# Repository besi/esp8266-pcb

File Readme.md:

ESP8266 PCB
===========

Flashing
--------

The 16MB flash chip need some special settings when flashing:

	esptool.py -p /dev/cu.usbserial-1412440 \
    -c esp8266 -b 460800 write_flash -fm dio \
    --flash_size=16MB \
    0x0000 ~/Downloads/ESP8266_GENERIC-20240222-v1.22.2.bin \
    0xffc000 ~/esp/esp-idf/components/esptool_py/esptool/test/images/esp8266_sdk/esp_init_data_default.bin

JLCPCB Footprints
-----------------

I created the following alias to download the footprints:

    # ~/.zshrc
    alias jlc='JLC2KiCadLib -dir lib -symbol_lib jlc_symbols -symbol_lib_dir "." -footprint_lib jlc_footprints.pretty'

So I can for example run `jlc C123455` to download both the symbol and the footprint for a given component.

    jlc C77967 --no_symbol # ESP8266EX chip
    jlc C505111 --no_symbol # Micro USB adapter
    jlc C7464026 --no_symbol # USB2UART chip
    jlc C160390 # I2C connector
    jlc C82227 # Temperature and humidity sensor
    jlc C2922787 # SK6812 Neopixel
    jlc C51118 # 3V3 AP2112K voltage regulator
    jlc C62892 # NPN transistor array
    jlc C318884 # Tactile switches
    jlc C424093 # Battery management IC
    jlc C97521 # flash chip (alternative: C5127618)
    jlc C295747 # JST battery connector
    jlc C963206 # slide switch
    jlc C15127 # FET for switching between VUSB and VBAT
    jlc C155590 # Zener Diode D3
    
    jlc C22975 # 2k R4
    jlc C19666 # 4.7uF
    jlc C25804 # 10k
    jlc C155590 # Shottkydiode D3
    jlc C15127 # p channel mosfet
    jlc C15849 # 1uF
    jlc C23630 # 2.2uF
    jlc C19702 # 10uF
    jlc C14663 # 100nF
    jlc C255886 # 26Mhz oscilator
    jlc C1634 # 10pF
    jlc C22790 # 12k
    jlc C8218 # 200 Ohm
    jlc C519111 # 5.6pF
        
Credits
-------

- I used the wonderful [JLC2KiCadLib](https://pypi.org/project/JLC2KiCadLib/) to get the footprints from the JLC components.
- This design was inspired by the [Sparkfun ESP8266 Thing](https://www.sparkfun.com/sparkfun-esp8266-thing.html)

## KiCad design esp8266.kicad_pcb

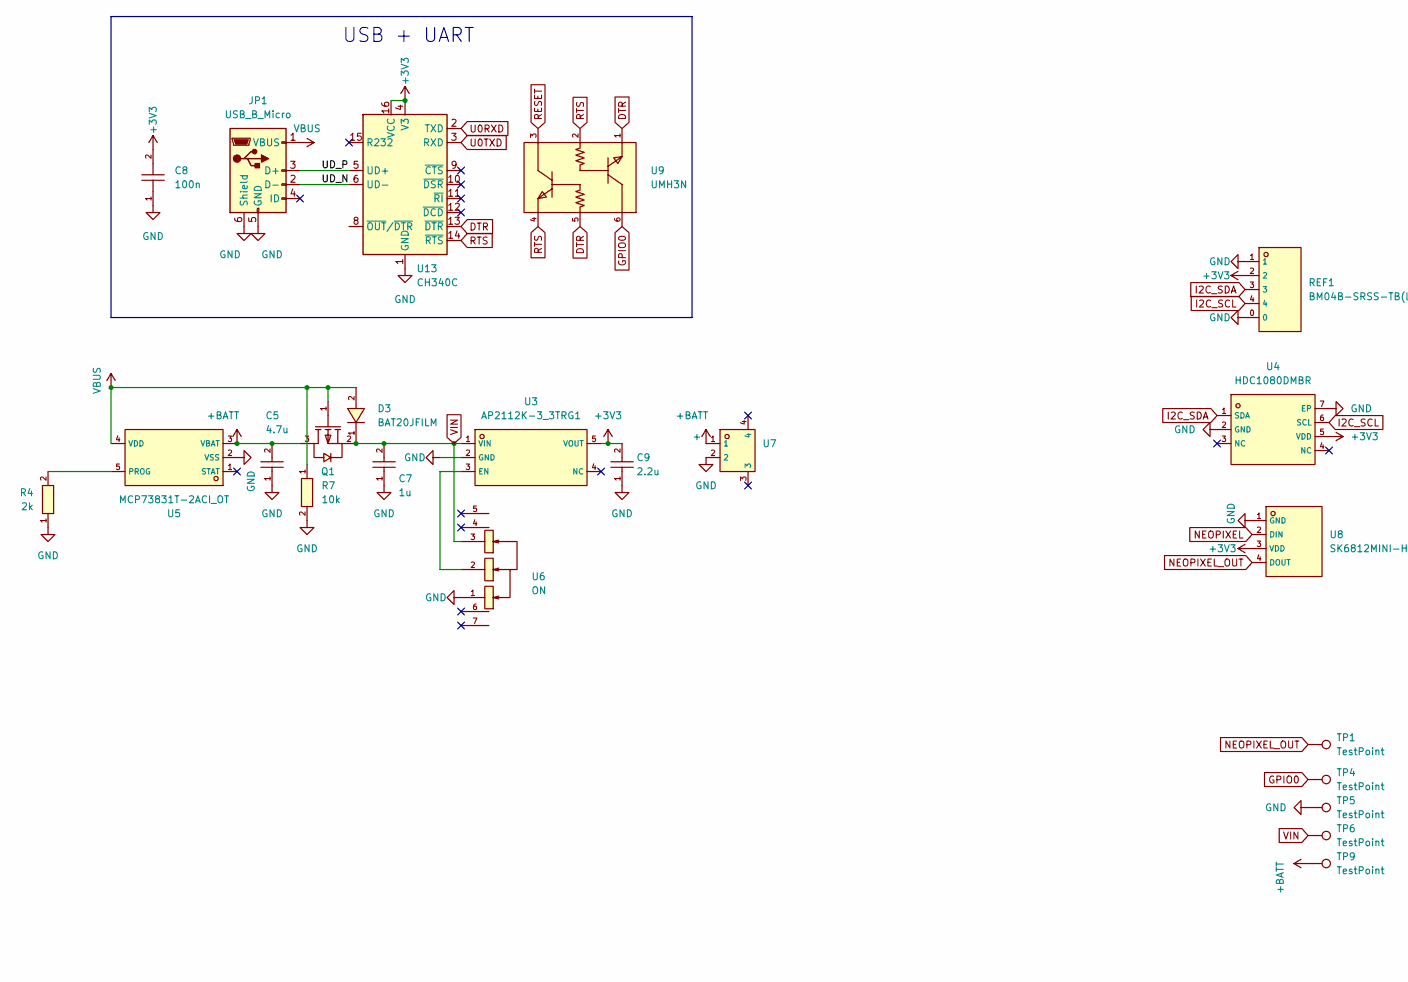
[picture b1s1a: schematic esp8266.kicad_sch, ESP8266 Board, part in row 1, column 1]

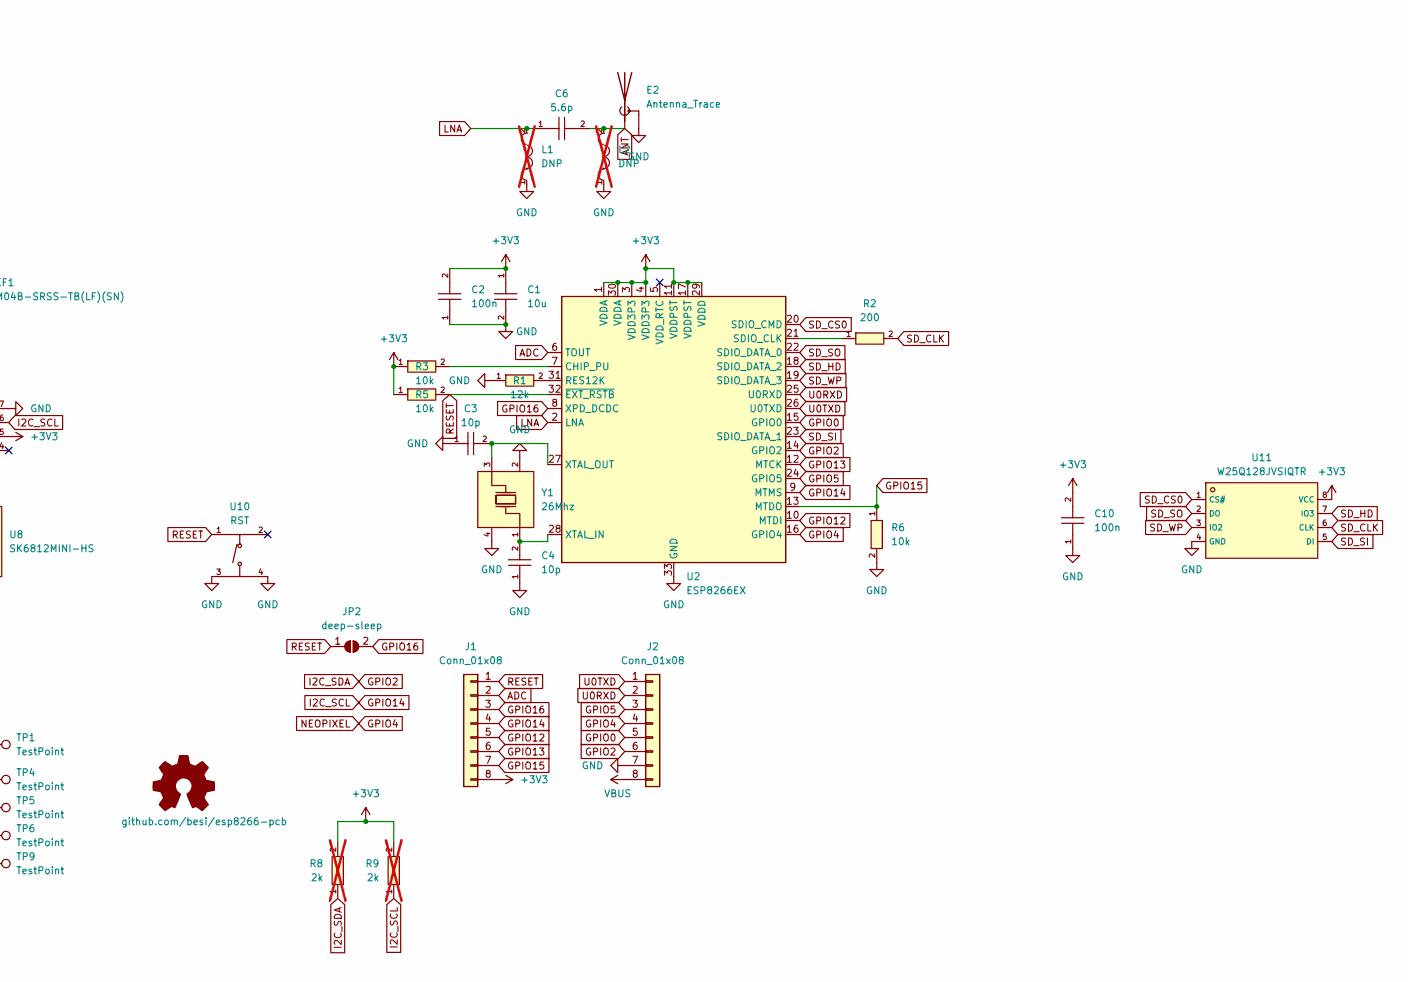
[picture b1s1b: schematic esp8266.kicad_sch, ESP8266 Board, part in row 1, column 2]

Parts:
C1: 10u; C0603; LCSC C19702
C2, C8, C10: 100n; C0603; LCSC C14663
C3, C4: 10p; C0603; LCSC C1634
C5: 4.7u; C0603; LCSC C19666
C6: 5.6p; C0603; LCSC C519111
C7: 1u; C0603; LCSC C15849
C9: 2.2u; C0603; LCSC C23630
D3: BAT20JFILM; SOD-323_L1.8-W1.3-LS2.5-RD; LCSC C155590
E2: Antenna_Trace; Texas_SWRA117D_2.4GHz_Right
J1, J2: Conn_01x08; PinHeader_1x08_P2.54mm_Vertical
JP1: USB_B_Micro; MICRO-USB-SMD_1050171001; LCSC C505111
JP2: deep-sleep; SolderJumper-2_P1.3mm_Open_TrianglePad1.0x1.5mm
L1, L2: DNP; L0603; LCSC C1035; not fitted
OSHW1: github.com/besi/esp8266-pcb; OSHW-Symbol_6.7x6mm_SilkScreen
Q1: AO3401A; SOT-23_L2.9-W1.3-P1.90-LS2.4-BR; LCSC C15127
R1: 12k; R0603; LCSC C22790
R2: 200; R0603; LCSC C8218
R3, R5, R6, R7: 10k; R0603; LCSC C25804
R4: 2k; R0603; LCSC C22975
R8, R9: 2k; R_0603_1608Metric_Pad0.98x0.95mm_HandSolder; LCSC C22975; not fitted
REF1: BM04B-SRSS-TB(LF)(SN); CONN-SMD_BM04B-SRSS-TB; LCSC C160390
TP1, TP4, TP5, TP6, TP9: TestPoint; TestPoint_Pad_D1.0mm
U2: ESP8266EX; QFN-32_L5.0-W5.0-P0.50-BL-EP3.7
U3: AP2112K-3_3TRG1; SOT-25-5_L2.9-W1.6-P0.95-LS2.8-BL; LCSC C51118
U4: HDC1080DMBR; SENSOR-SMD_HDC1080DMBR; LCSC C82227
U5: MCP73831T-2ACI_OT; SOT-23-5_L3.0-W1.7-P0.95-LS2.8-BL; LCSC C424093
U6: ON; SW-SMD_MK-12C02-G020; LCSC C963206
U7: +; CONN-SMD_P2.00_S2B-PH-SM4-TB-LF-SN; LCSC C295747
U8: SK6812MINI-HS; LED-SMD_4P-L3.5-W3.5-BR_SK6812MINI-HS; LCSC C2922787
U9: UMH3N; SC-70-6_L2.2-W1.3-P0.65-LS2.1-BR; LCSC C62892
U10: RST; SW-SMD_4P-L5.1-W5.1-P3.70-LS6.5-TL-2; LCSC C318884
U11: W25Q128JVSIQTR; SOIC-8_L5.3-W5.3-P1.27-LS8.0-BL; LCSC C97521
U13: CH340C; SOP-16_L10.0-W3.9-P1.27-LS6.0-BL; LCSC C7464026
Y1: 26Mhz; CRYSTAL-SMD_4P-L2.0-W1.6-BL; LCSC C255886

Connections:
+3V3: C1.1, C2.2, C8.2, C9.2, C10.2, J1.8, R3.1, R5.1, R8.2, R9.2, REF1.2, U2.1 (VDDA), U2.3 (VDD3P3), U2.4 (VDD3P3), U2.11 (VDDPST), U2.17 (VDDPST), U2.29 (VDDD), U2.30 (VDDA), U3.5 (VOUT), U4.5 (VDD), U8.3 (VDD), U11.8 (VCC), U13.4 (V3), U13.16 (VCC)
+BATT: C5.2, Q1.3 (D), TP9.1, U5.3 (VBAT), U7.1
/UD_N: JP1.2 (D-), U13.6 (UD-)
/UD_P: JP1.3 (D+), U13.5 (UD+)
ADC: J1.2, U2.6 (TOUT)
ANT: C6.2, E2.1 (A), L2.2
DTR: U9.1 (E), U9.5 (B), U13.13 (~DTR)
GND: C1.2, C2.1, C3.1, C4.1, C5.1, C7.1, C8.1, C9.1, C10.1, E2.2 (Shield), J2.7, JP1.5 (GND), JP1.6 (Shield), L1.1, L2.1, R1.1, R4.1, R6.2, R7.2, REF1.0, REF1.1, TP5.1, U2.33 (GND), U3.2 (GND), U4.2 (GND), U4.7 (EP), U5.2 (VSS), U6.1, U7.2, U8.1 (GND), U10.3 (C), U10.4 (D), U11.4 (GND), U13.1 (GND), Y1.2 (GND), Y1.4 (GND)
GPIO0: J2.5, TP4.1, U2.15 (GPIO0), U9.6 (C)
GPIO2: J2.6, R8.1, REF1.3, U2.14 (GPIO2), U4.1 (SDA)
GPIO4: J2.4, U2.16 (GPIO4), U8.2 (DIN)
GPIO5: J2.3, U2.24 (GPIO5)
GPIO12: J1.5, U2.10 (MTDI)
GPIO13: J1.6, U2.12 (MTCK)
GPIO14: J1.4, R9.1, REF1.4, U2.9 (MTMS), U4.6 (SCL)
GPIO15: J1.7, R6.1, U2.13 (MTDO)
GPIO16: J1.3, JP2.2 (B), U2.8 (XPD_DCDC)
LNA: C6.1, L1.2, U2.2 (LNA)
NEOPIXEL_OUT: TP1.1, U8.4 (DOUT)
unnamed: R3.2, U2.7 (CHIP_PU)
unnamed: R1.2, U2.31 (RES12K)
unnamed: R2.1, U2.21 (SDIO_CLK)
unnamed: C4.2, U2.28 (XTAL_IN), Y1.1 (OSC1)
unnamed: C3.2, U2.27 (XTAL_OUT), Y1.3 (OSC2)
unnamed: U3.3 (EN), U6.2
unnamed: R4.2, U5.5 (PROG)
RESET: J1.1, JP2.1 (A), R5.2, U2.32 (~EXT_RSTB), U9.3 (C), U10.1 (A)
RTS: U9.2 (B), U9.4 (E), U13.14 (~RTS)
SD_CLK: R2.2, U11.6 (CLK)
SD_CS0: U2.20 (SDIO_CMD), U11.1 (CS#)
SD_HD: U2.18 (SDIO_DATA_2), U11.7 (IO3)
SD_SI: U2.23 (SDIO_DATA_1), U11.5 (DI)
SD_SO: U2.22 (SDIO_DATA_0), U11.2 (DO)
SD_WP: U2.19 (SDIO_DATA_3), U11.3 (IO2)
U0RXD: J2.2, U2.25 (U0RXD), U13.2 (TXD)
U0TXD: J2.1, U2.26 (U0TXD), U13.3 (RXD)
VBUS: D3.2 (A), J2.8, JP1.1 (VBUS), Q1.1 (G), R7.1, U5.4 (VDD)
VIN: C7.2, D3.1 (K), Q1.2 (S), TP6.1, U3.1 (VIN), U6.3

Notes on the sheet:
USB + UART

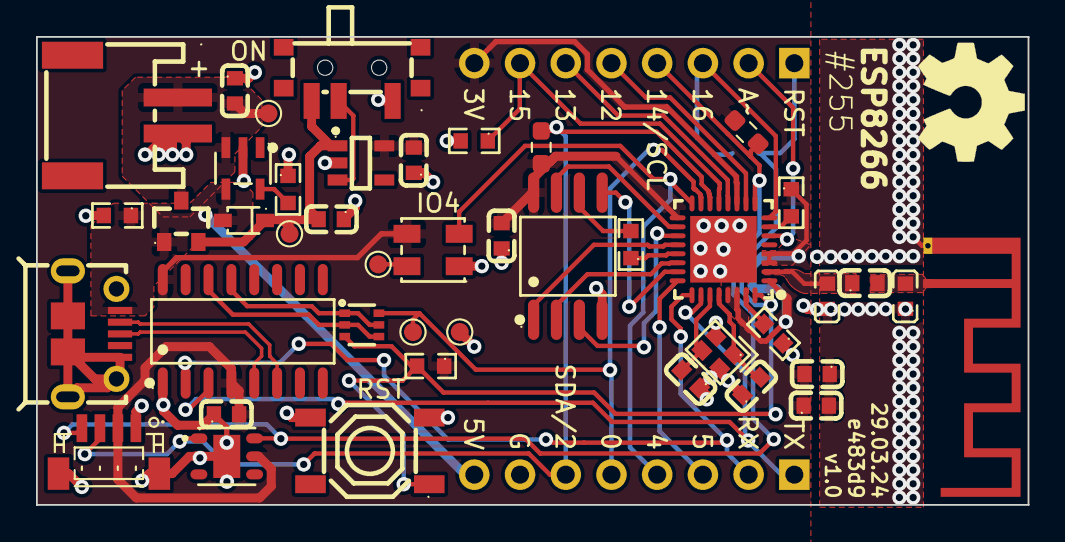
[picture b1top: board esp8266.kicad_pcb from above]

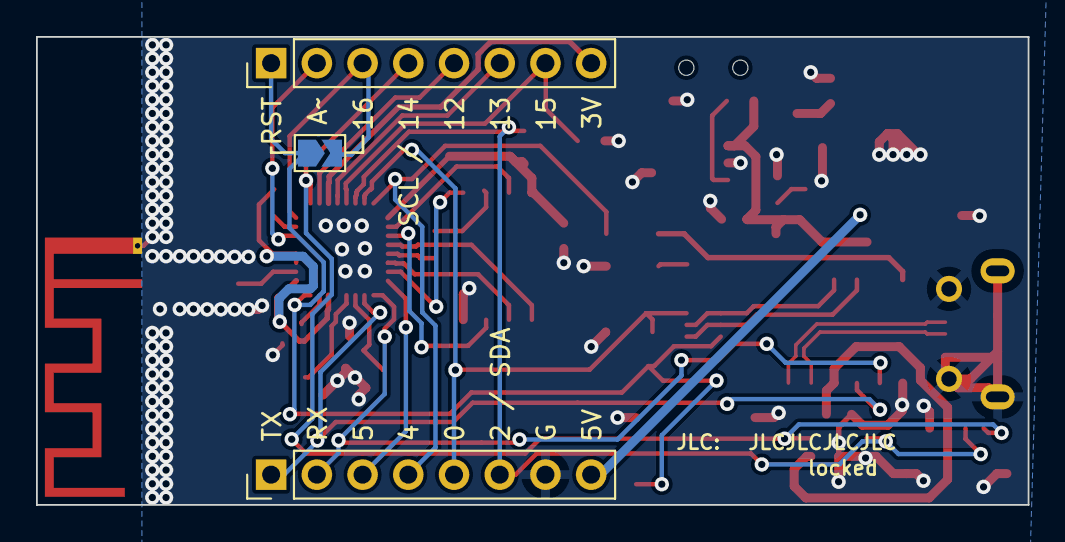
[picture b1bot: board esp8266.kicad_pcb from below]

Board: 2 copper layers, 55.1 x 26.0 mm, 47 parts (3 on the bottom side), 38 nets.

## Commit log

2024-03-27 Add empty project
2024-03-27 Setup the JLC components library
    Add main components
2024-03-28 Schematic done
2024-03-28 Add antenna and layout the board
2024-03-29 Add silkscreen, test points and optional pull ups for I2C
    Also don’t route underneath antenna pin
2024-03-29 Add a solder jumper for IO16 and RESET
2024-03-29 Prepare for production
2024-03-29 Don’t add solder jumper to BOM
2024-03-29 Update readme and add a screenshot
2024-12-28 Update the readme on how to flash the board
2025-01-20 Add software
2026-02-12 Credit where it's due =)
